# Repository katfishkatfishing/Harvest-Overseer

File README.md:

# Harvest-Overseer 
>Built for third space Hack Club! - Week 1️  
_It all started when two unemployed dudes stumbled upon a third, equally unemployed dude. Unburdened by 9-to-5s (erm but we have 9-5s for school) and fuelled by sheer ambition, the trio tries their best to tackle thirdspace._

## Project Overview 
**Harvest-Overseer** is a stationary, comprehensive agricultural monitor that measures soil pH, moisture levels, nutrient concentrations (NPK), and light intensity. It displays the data of the plant and soil's health on an LCD screen to let you easily know what your plant needs. It displays real-time health diagnostics on an integrated LCD screen so you always know exactly what your plants need to thrive.

### Key Features
**Monitors the soil:** Monitors pH balance and NPK (_Nitrogen, Phosphorus, Potassium_) concentrations.\
**Monitors soil humidity:** Measures the humidity of the soil and computes whether you need to water your plant or not.\
**Monitors light intensity:** Tracks daily ambient light exposures to ensure optimal photosynthesis conditions.\
**Display:** Instant visual updates and shows you clearly what your plant needs.\
**Battery Powered:** Sensor node is battery powered.  

## PCB & Hardware Architecture 
### Master Node (the screen part)
The Master Node receives sensor data, handles system logic, and drives the local LCD status display.
+ <ins>MCU</ins> `ESP32-S3-WROOM-1-N16R8` connects to sensor node to receive data and drive display.
+ <ins>Display</ins> `7-Pin SPI lcd` 3.5 Inch 480*320 SPI TFT LCD Module.
+ <ins>Power</ins> `TP4056 charging power module board` for USB-C power and battery charging, and a `TPS7133Q` (LDO) that converts 4.2V to 3.3V.

_Master Unit PCB and Schematics_
<table>
  <tr>
    <td align="center">
      <br>
      Schematic
    </td>
    <td align="center">
      <br>
      PCB Trace Routing
    </td>
  </tr>
  <tr>
    <td align="center">
       <br>
      3D PCB Render (Top view)
    </td>
    <td align="center">
      <br>
      3D PCB Render (Bottom view)
    </td>
  </tr>
</table>

### Sensor Node
The Sensor Node is an autonomous, low-power unit placed in the soil bed to read the pH, moisture, light, and NPK levels, transmitting readings via ESP-NOW back to the Master Node.

#### Components
+ <ins>MCU</ins> `ESP32-C3-WROOM-02` (compact RISC-V Wi-Fi/BLE MCU) for reading sensors and beaming data to the Master Node.
+ <ins>Power Management</ins> `MCP73871-2CC`, a LiPo/Li-ion charge manager with automatic power path management, allowing simultaneous solar/USB power supply and battery charging.
+ <ins>Timer</ins> `TPL5110`, a system timer that completely cuts off power to the entire node until a scheduled wake interval, reducing standby drain to extend battery life.
+ <ins>Another High-Efficiency Power Management Component</ins>, the `DMG3415U` (P-Channel MOSFET) used to physically power down high-draw soil sensors when the node is sleeping.
+ <ins>Voltage Regulation (LDO)</ins> `HT7333` (Low quiescent current 3.3V regulator for logic and sensor rails).

#### Connectors & Peripherals 
+ <ins>USB-C Interface</ins> a `USB4085` GCT 16-pin USB-C receptacle for charging and power delivery.
+ <ins>Sensor Terminal Blocks</ins> `WAGO 233 Series` tool-less spring-cage terminals for wiring of soil sensors.

<table>
  <tr>
    <td align="center">
      <br>
      Schematic
    </td>
  </tr>
</table>
<table>
  <tr>
    <td align="center">
       <br>
      PCB Trace Routing
    </td>
    <td align="center">
      <br>
      3D PCB Render
    </td>
  </tr>
</table>
<table>
  <tr>
    <td align="center">
       <br>
      3D Model
    </td>
    <td align="center">
      <br>
      3D Model
    </td>
  </tr>
</table>

## Display & User Interface
`DLS24035B` for the display (3.5 Inch 480*320 SPI TFT LCD Module with ILI9488 Driver) with a custom case model.
<table>
  <tr>
    <td align="center">
      <br>
      Front View
    </td>
    <td align="center">
      <br>
      Bottom View
    </td>
  </tr>
</table>

_Here's a photo of the Master Node PCB in the case._
<table>
  <tr>
    <td align="center">
      <br>
      Master Node 3D PCB in case
    </td>
    <td align="center">
      <br>
      Master Node 3D PCB model
    </td>
  </tr>
</table>

_Some display ui (done in the Figma software)_
<table>
  <tr>
    <td align="center">
      <br>
      Plant in good helth
    </td>
    <td align="center">
      <br>
      Plant is unhelth
    </td>
  </tr>
</table>

## Components Used
+ ESP32-S3-WROOM-1-N16N
+ 14-pin socket (Conn_01x14_Socket)
+ TP4056 charging power module board
+ TPS7133Q LDO
+ ESP32-C3-WROOM-02
+ MCP73871-2CC
+ TPL5110
+ DMG3415U
+ HT7333_C2684634
+ USB-C receptacle GCT_USB4085
+ Terminal block WAGO_233-508_2x08
+ Terminal block WAGO_233-508_2x04
+ Button switch SW_SPST_B3U-1000P
+ LED_SMD_0603
+ 10µF capacitor SMD 0402
+ 68k, 10k, 2k, 100k, 5.1k resistor SMD 0603
+ 470R resistor SMD 0402
+ DLS24035B (3.5inch 480*320 SPI TFT LCD Module with ILI9488 Driver)

## BOM
| MCU                               | ESP32-C3-WROOM-02                                   | 1   | 1.80  | 1.80  | https://www.aliexpress.com/item/1005003181553659.html                |
| --------------------------------- | --------------------------------------------------- | --- | ----- | ----- | -------------------------------------------------------------------- |
| 2.54mm Female Header              | Conn_01x08_Socket                                   | 2   | 0.15  | 0.75  | https://www.aliexpress.com/w/wholesale-2.54mm-female-header.html     |
| 2.54mm Female Header              | Conn_01x04_Socket                                   | 1   | 0.10  | 0.50  | https://www.aliexpress.com/w/wholesale-2.54mm-female-header.html     |
| 2.54mm Female Header              | Conn_01x02_Socket                                   | 1   | 0.08  | 0.40  | https://www.aliexpress.com/w/wholesale-2.54mm-female-header.html     |
| LiPo/Li-ion Battery Management IC | MCP73871-2CC                                        | 1   | 2.20  | 2.20  | https://www.aliexpress.com/item/1005009931582723.html                |
| Ultra-Low-Power Timer             | TPL5110                                             | 1   | 3.50  | 3.50  | https://www.aliexpress.com/item/1005009324980307.html                |
| P-Channel MOSFET                  | DMG3415U                                            | 1   | 0.09  | 8.50  | https://www.aliexpress.com/item/1005009968198030.html                |
| Low-Power LDO                     | HT7333_C2684634                                     | 1   | 0.10  | 1.00  | https://www.aliexpress.com/item/32697055615.html                     |
| USB-C Receptacle                  | GCT_USB4085                                         | 1   | 0.35  | 1.75  | https://www.aliexpress.com/w/wholesale-16p-usb-c-receptacle.html     |
| Terminal block                    | WAGO_233-508_2x08                                   | 1   | 1.20  | 1.20  | https://www.aliexpress.com/w/wholesale-wago-233.html                 |
| Terminal block                    | WAGO_233-508_2x04                                   | 1   | 0.70  | 0.70  | https://www.aliexpress.com/w/wholesale-wago-233.html                 |
| Button switch                     | SW_SPST_B3U-1000P                                   | 2   | 0.10  | 1.00  | https://www.aliexpress.com/w/wholesale-smd-tactile-switch.html       |
| LED                               | SMD_0603                                            | 3   | 0.01  | 0.80  | https://www.aliexpress.com/w/wholesale-0603-smd-led.html             |
| Ceramic Capacitor SMD             | 10µF 0402                                           | 3   | 0.01  | 0.90  | https://www.aliexpress.com/w/wholesale-0402-10uf.html                |
| Ceramic Resistor SMD              | 68k 0603                                            | 1   | 0.01  | 0.50  | https://www.aliexpress.com/w/wholesale-smd-resistor-sample-book.html |
| Ceramic Resistor SMD              | 10k 0603                                            | 4   | 0.01  | 0.50  | https://www.aliexpress.com/w/wholesale-smd-resistor-sample-book.html |
| Ceramic Resistor SMD              | 2k 0603                                             | 1   | 0.01  | 0.50  | https://www.aliexpress.com/w/wholesale-smd-resistor-sample-book.html |
| Ceramic Resistor SMD              | 100k 0603                                           | 1   | 0.01  | 0.50  | https://www.aliexpress.com/w/wholesale-smd-resistor-sample-book.html |
| Ceramic Resistor SMD              | 5.1k 0603                                           | 2   | 0.01  | 0.50  | https://www.aliexpress.com/w/wholesale-smd-resistor-sample-book.html |
| Ceramic Resistor SMD              | 470R 0402                                           | 3   | 0.01  | 0.50  | https://www.aliexpress.com/w/wholesale-smd-resistor-sample-book.html |
| Liquid Crystal Display            | DLS24035B                                           | 1   | 9.20  | 9.20  | https://www.aliexpress.com/item/1005005287088814.html                |
| Capacitor SMD                     | 1uF 0603 (C_0402_1005Metric)                        | 1   | 2.27  | 2.27  | https://www.aliexpress.com/item/1005012364450156.html                |
| 2.54mm Female Header              | Conn_01x14_Socket (PinSocket_1x14_P2.54mm_Vertical) | 1   | 2.89  | 2.89  | https://www.aliexpress.com/item/1005003610333849.html                |
| Resistor SMD                      | 10k 0603 (R_0603_1608Metric)                        | 3   | 0.45  | 1.36  | https://www.aliexpress.com/item/1005005677654015.html                |
| Push Button Switch (THT)          | MJTP1243 (SW_PUSH_1P1T_6x3.5mm_H4.3_APEM_MJTP1243)  | 1   | 0.42  | 0.42  | https://www.digikey.com/en/products/detail/apem-inc/MJTP1243/1798039 |
| Side Tactile Switch (SMD)         | TS-1101-C-W (SW-SMD_TC-1101V-C-B-W)                 | 1   | 0.40  | 0.40  | https://item.szlcsc.com/300030.html                                  |
| Power Module                      | TP4056 module (PWRM-TH_TP4056)                      | 1   | 1.73  | 1.73  | https://www.aliexpress.com/item/1005005982385924.html                |
| MCU Module                        | ESP32-S3-WROOM-1-N16R8 (ESP32-S3-WROOM-1_EXP)       | 1   | 4.78  | 4.78  | https://www.aliexpress.com/item/1005005230800143.html                |
| Voltage Regulator IC              | TPS7133 (SOIC-8_3.9x4.9mm_P1.27mm)                  | 1   | 15.36 | 15.36 | https://www.aliexpress.com/item/1005012324115212.html                |

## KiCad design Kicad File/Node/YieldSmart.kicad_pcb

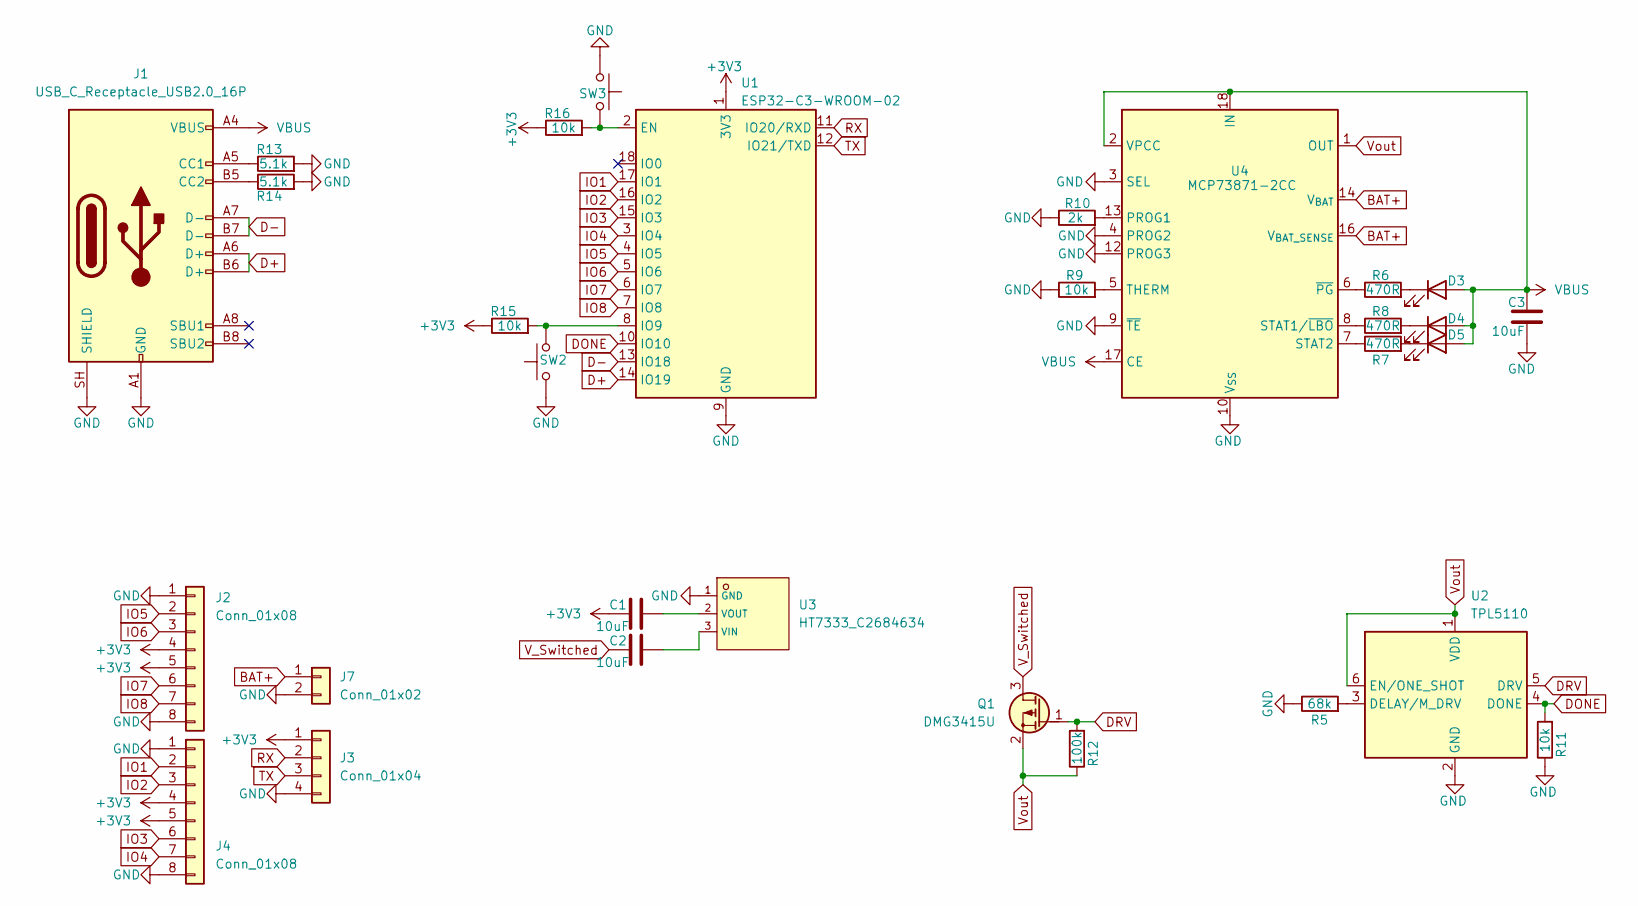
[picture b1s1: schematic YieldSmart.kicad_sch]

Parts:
C1, C2, C3: 10uF; C_0402_1005Metric_Pad0.74x0.62mm_HandSolder
D3, D4, D5: LED; LED_0603_1608Metric_Pad1.05x0.95mm_HandSolder
J1: USB_C_Receptacle_USB2.0_16P; USB_C_Receptacle_GCT_USB4085
J2, J4: Conn_01x08; PinHeader_1x08_P2.54mm_Vertical
J3: Conn_01x04; PinHeader_1x04_P2.54mm_Vertical
J7: Conn_01x02; PinHeader_1x02_P2.54mm_Vertical
Q1: DMG3415U; SOT-23
R5: 68k; R_0603_1608Metric_Pad0.98x0.95mm_HandSolder
R6, R7, R8: 470R; R_0402_1005Metric_Pad0.72x0.64mm_HandSolder
R9, R11, R15, R16: 10k; R_0603_1608Metric_Pad0.98x0.95mm_HandSolder
R10: 2k; R_0603_1608Metric_Pad0.98x0.95mm_HandSolder
R12: 100k; R_0603_1608Metric_Pad0.98x0.95mm_HandSolder
R13, R14: 5.1k; R_0603_1608Metric_Pad0.98x0.95mm_HandSolder
SW2, SW3: SW_Push; SW_SPST_B3U-1000P
U1: ESP32-C3-WROOM-02
U2: TPL5110; SOT-23-6
U3: HT7333_C2684634; C2684634_SOT-23-3_L2_9-W1_6-P1_90-LS2_8-BR; LCSC C2684634
U4: MCP73871-2CC; QFN-20-1EP_4x4mm_P0.5mm_EP2.5x2.5mm

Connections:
+3V3: C1.1, J2.4, J2.5, J3.1, J4.4, J4.5, R15.1, R16.1, U1.1 (3V3)
BAT+: J7.1, U4.14 (V_{BAT}), U4.15 (V_{BAT}), U4.16 (V_{BAT_SENSE})
D+: J1.A6 (D+), J1.B6 (D+), U1.14 (IO19)
D-: J1.A7 (D-), J1.B7 (D-), U1.13 (IO18)
DONE: R11.2, U1.10 (IO10), U2.4 (DONE)
DRV: Q1.1 (G), R12.2, U2.5 (DRV)
GND: C3.2, J1.A1 (GND), J1.A12 (GND), J1.B1 (GND), J1.B12 (GND), J1.SH (SHIELD), J2.1, J2.8, J3.4, J4.1, J4.8, J7.2, R5.1, R9.1, R10.1, R11.1, R13.2, R14.2, SW2.2, SW3.2, U1.9 (GND), U1.19 (GND), U2.2 (GND), U3.1 (GND), U4.3 (SEL), U4.4 (PROG2), U4.9 (~TE), U4.10 (V_{SS}), U4.11 (V_{SS}), U4.12 (PROG3), U4.21 (V_{SS})
IO1: J4.2, U1.17 (IO1)
IO2: J4.3, U1.16 (IO2)
IO3: J4.6, U1.15 (IO3)
IO4: J4.7, U1.3 (IO4)
IO5: J2.2, U1.4 (IO5)
IO6: J2.3, U1.5 (IO6)
IO7: J2.6, U1.6 (IO7)
IO8: J2.7, U1.7 (IO8)
unnamed: D3.1 (K), R6.2
unnamed: D4.1 (K), R8.2
unnamed: D5.1 (K), R7.2
unnamed: J1.A5 (CC1), R13.1
unnamed: J1.B5 (CC2), R14.1
unnamed: R16.2, SW3.1, U1.2 (EN)
unnamed: R15.2, SW2.1, U1.8 (IO9)
unnamed: R5.2, U2.3 (DELAY/M_DRV)
unnamed: C2.2, U3.3 (VIN)
unnamed: C1.2, U3.2 (VOUT)
unnamed: R10.2, U4.13 (PROG1)
unnamed: R8.1, U4.8 (STAT1/~LBO)
unnamed: R7.1, U4.7 (STAT2)
unnamed: R9.2, U4.5 (THERM)
unnamed: R6.1, U4.6 (~PG)
RX: J3.2, U1.11 (IO20/RXD)
TX: J3.3, U1.12 (IO21/TXD)
VBUS: C3.1, D3.2 (A), D4.2 (A), D5.2 (A), J1.A4 (VBUS), J1.A9 (VBUS), J1.B4 (VBUS), J1.B9 (VBUS), U4.2 (VPCC), U4.17 (CE), U4.18 (IN), U4.19 (IN)
V_Switched: C2.1, Q1.3 (D)
Vout: Q1.2 (S), R12.1, U2.1 (VDD), U2.6 (EN/ONE_SHOT), U4.1 (OUT), U4.20 (OUT)

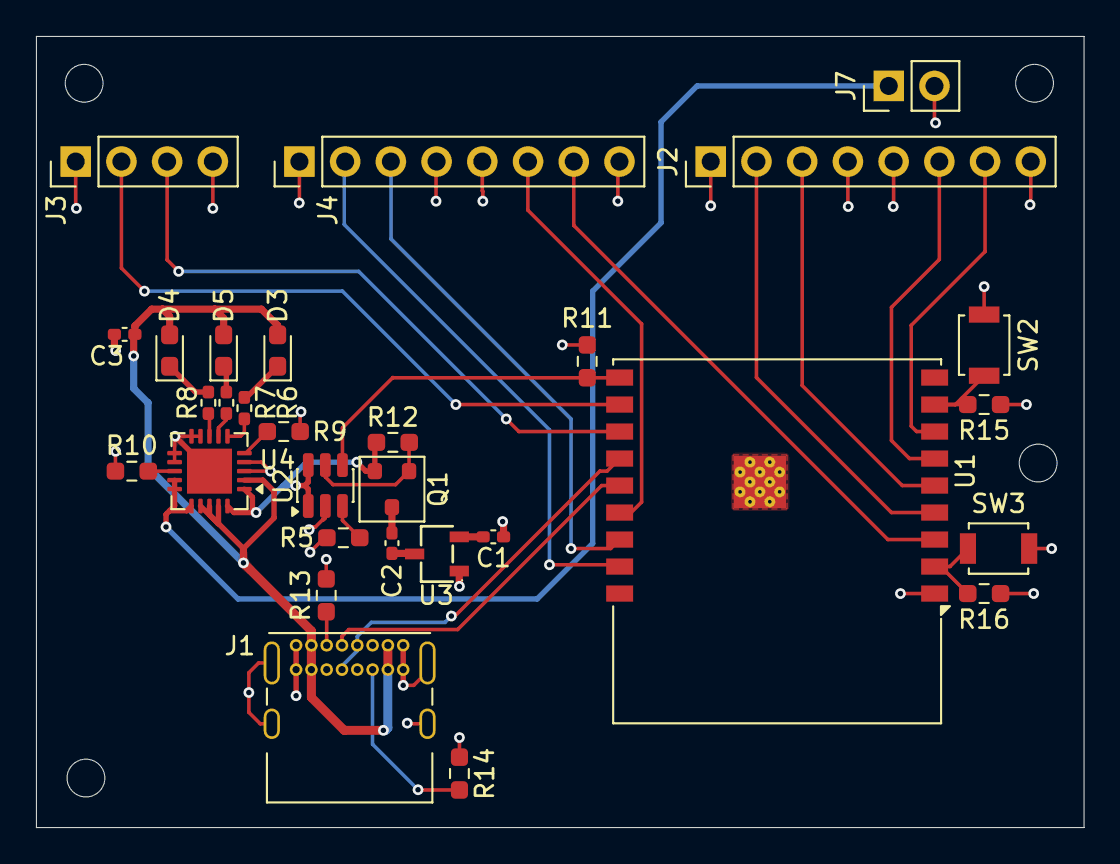
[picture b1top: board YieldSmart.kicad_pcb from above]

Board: 4 copper layers, 58.2 x 43.9 mm, 30 parts (0 on the bottom side), 35 nets.

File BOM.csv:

Item,Parts,Qty.,Unit price(USD),Price per lot(USD),Source
MCU, ESP32-C3-WROOM-02, 1, 1.80, 1.80, https://www.aliexpress.com/item/1005003181553659.html
2.54mm Female Header, Conn_01x08_Socket, 2, 0.15, 0.75, https://www.aliexpress.com/w/wholesale-2.54mm-female-header.html
2.54mm Female Header, Conn_01x04_Socket, 1, 0.10, 0.50, https://www.aliexpress.com/w/wholesale-2.54mm-female-header.html
2.54mm Female Header, Conn_01x02_Socket, 1, 0.08, 0.40, https://www.aliexpress.com/w/wholesale-2.54mm-female-header.html
LiPo/Li-ion Battery Management IC, MCP73871-2CC, 1, 2.20, 2.20, https://www.aliexpress.com/item/1005009931582723.html
Ultra-Low-Power Timer, TPL5110, 1, 3.50, 3.50, https://www.aliexpress.com/item/1005009324980307.html
P-Channel MOSFET, DMG3415U, 1, 0.09, 8.50, https://www.aliexpress.com/item/1005009968198030.html
Low-Power LDO, HT7333_C2684634, 1, 0.10, 1.00, https://www.aliexpress.com/item/32697055615.html
USB-C Receptacle, GCT_USB4085, 1, 0.35, 1.75, https://www.aliexpress.com/w/wholesale-16p-usb-c-receptacle.html
Terminal block, WAGO_233-508_2x08, 1, 1.20, 1.20, https://www.aliexpress.com/w/wholesale-wago-233.html
Terminal block, WAGO_233-508_2x04, 1, 0.70, 0.70, https://www.aliexpress.com/w/wholesale-wago-233.html
Button switch, SW_SPST_B3U-1000P, 2, 0.10, 1.00, https://www.aliexpress.com/w/wholesale-smd-tactile-switch.html
LED, SMD_0603, 3, 0.01, 0.80, https://www.aliexpress.com/w/wholesale-0603-smd-led.html
Ceramic Capacitor SMD, 10µF 0402, 3, 0.01, 0.90, https://www.aliexpress.com/w/wholesale-0402-10uf.html
Ceramic Resistor SMD, 68k 0603, 1, 0.01, 0.50, https://www.aliexpress.com/w/wholesale-smd-resistor-sample-b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
Ceramic Resistor SMD, 10k 0603, 4, 0.01, 0.50, https://www.aliexpress.com/w/wholesale-smd-resistor-sample-b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
Ceramic Resistor SMD, 2k 0603, 1, 0.01, 0.50, https://www.aliexpress.com/w/wholesale-smd-resistor-sample-b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
Ceramic Resistor SMD, 100k 0603, 1, 0.01, 0.50, https://www.aliexpress.com/w/wholesale-smd-resistor-sample-b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
Ceramic Resistor SMD, 5.1k 0603, 2, 0.01, 0.50, https://www.aliexpress.com/w/wholesale-smd-resistor-sample-b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
Ceramic Resistor SMD, 470R 0402, 3, 0.01, 0.50, https://www.aliexpress.com/w/wholesale-smd-resistor-sample-b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
Liquid Crystal Display, DLS24035B, 1, 9.20, 9.20, https://www.aliexpress.com/item/1005005287088814.html
<!-- BOM generated in https://md-to.com/csv-to-markdown-table/ -->

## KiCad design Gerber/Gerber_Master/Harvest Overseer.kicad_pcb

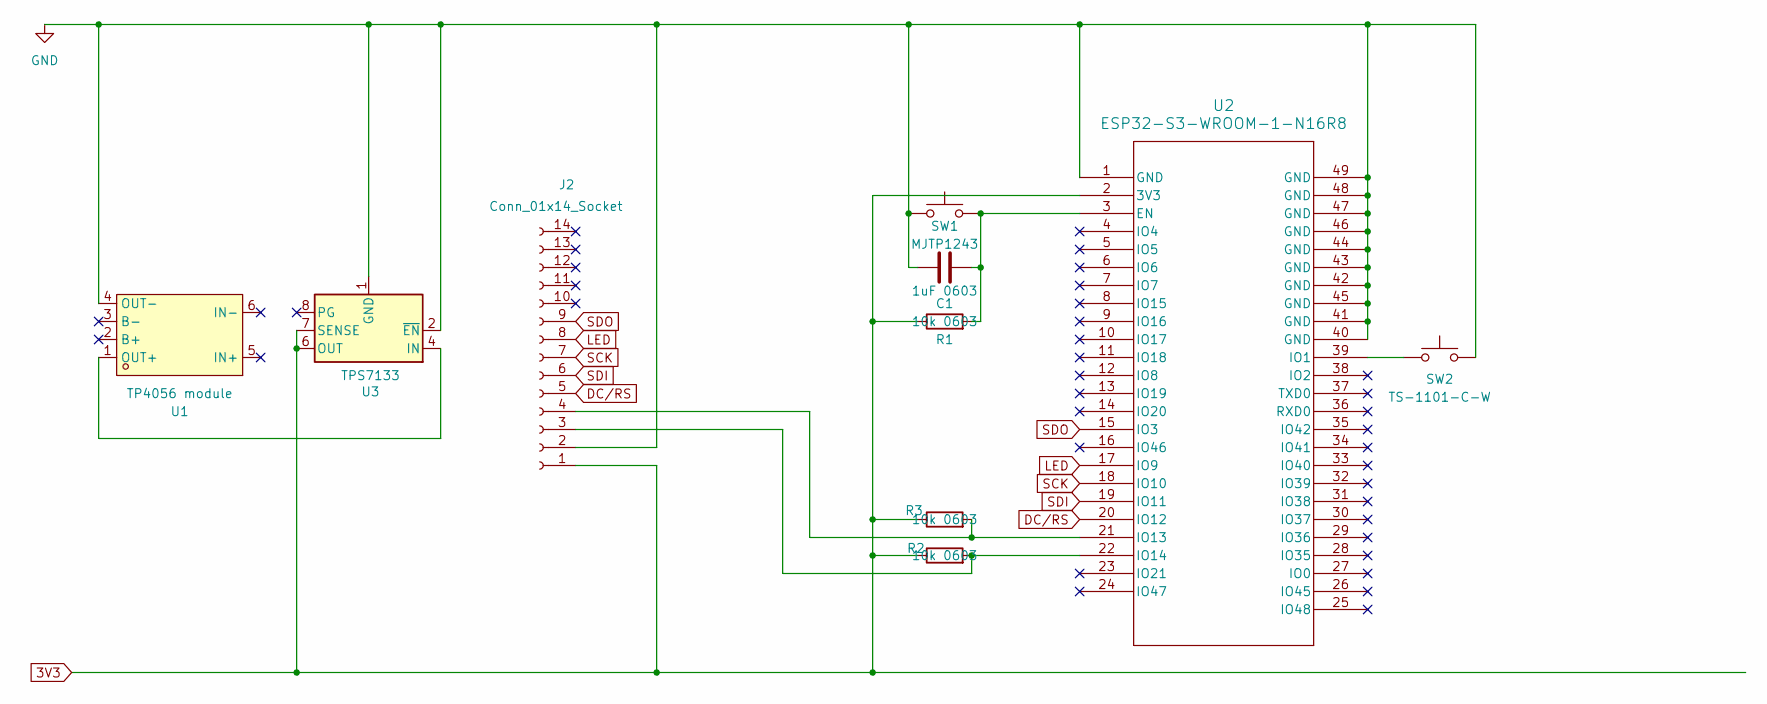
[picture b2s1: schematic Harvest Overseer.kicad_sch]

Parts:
C1: 1uF 0603; C_0402_1005Metric
J2: Conn_01x14_Socket; PinSocket_1x14_P2.54mm_Vertical
R1, R2, R3: 10k 0603; R_0603_1608Metric
SW1: MJTP1243; SW_PUSH_1P1T_6x3.5mm_H4.3_APEM_MJTP1243
SW2: TS-1101-C-W; SW-SMD_TC-1101V-C-B-W
U1: TP4056 module; PWRM-TH_TP4056; MPN TP4056充电源模块板(Type-C); LCSC Part C9900049108
U2: ESP32-S3-WROOM-1-N16R8; ESP32-S3-WROOM-1_EXP
U3: TPS7133; SOIC-8_3.9x4.9mm_P1.27mm

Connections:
3V3: J2.1, R1.1, R2.1, R3.1, U2.2 (3V3), U3.5 (OUT), U3.6 (OUT), U3.7 (SENSE)
DC/RS: J2.5, U2.20 (IO12)
GND: C1.1, J2.2, SW1.1, SW2.2, U1.4 (OUT-), U2.1 (GND), U2.40 (GND), U2.41 (GND), U2.42 (GND), U2.43 (GND), U2.44 (GND), U2.45 (GND), U2.46 (GND), U2.47 (GND), U2.48 (GND), U2.49 (GND), U3.1 (GND), U3.2 (~EN)
LED: J2.8, U2.17 (IO9)
unnamed: J2.3, R2.2, U2.22 (IO14)
unnamed: J2.4, R3.2, U2.21 (IO13)
unnamed: U1.1 (OUT+), U3.3 (IN), U3.4 (IN)
unnamed: C1.2, R1.2, SW1.2, U2.3 (EN)
unnamed: SW2.1, U2.39 (IO1)
SCK: J2.7, U2.18 (IO10)
SDI: J2.6, U2.19 (IO11)
SDO: J2.9, U2.15 (IO3)

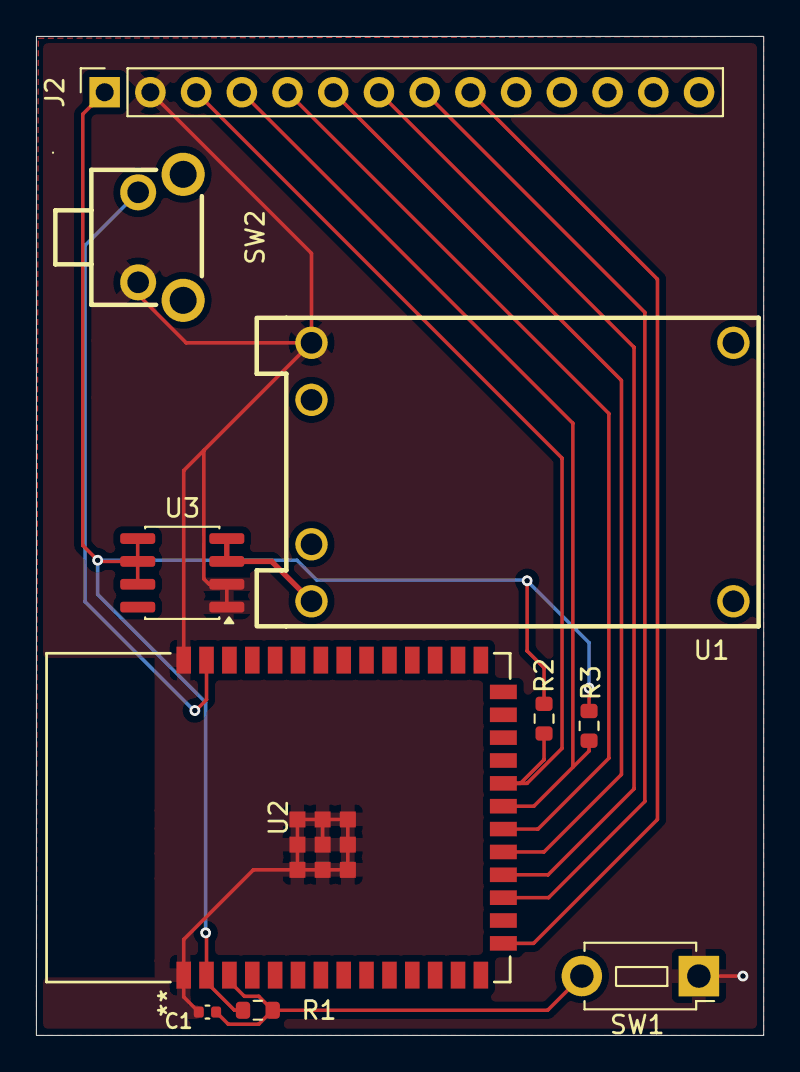
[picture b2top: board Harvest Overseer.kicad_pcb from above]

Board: 2 copper layers, 40.4 x 55.5 mm, 10 parts (0 on the bottom side), 12 nets.

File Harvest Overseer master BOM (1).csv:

"Qty","Value","Footprint","Price per lot (usd)","Source"
"1","1uF 0603","Capacitor_SMD:C_0402_1005Metric","2.27","https://www.aliexpress.com/item/1005012364450156.html?spm=a2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"
"1","Conn_01x14_Socket","Connector_PinSocket_2.54mm:PinSocket_1x14_P2.54mm_Vertical","2.89","https://www.aliexpress.com/item/1005003610333849.html?spm=a2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"
"3","10k 0603","Resistor_SMD:R_0603_1608Metric","1.36","https://www.aliexpress.com/item/1005005677654015.html?spm=a2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"
"1","MJTP1243","Button_Switch_THT:SW_PUSH_1P1T_6x3.5mm_H4.3_APEM_MJTP1243","0.42","https://www.digikey.com/en/products/detail/apem-inc/MJTP1243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"
"1","TS-1101-C-W","sidebutton:SW-SMD_TC-1101V-C-B-W","0.40","https://item.szlcsc.com/300030.html"
"1","TP4056 module","easyeda2kicad:PWRM-TH_TP4056","1.73","https://www.aliexpress.com/item/1005005982385924.html?spm=a2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"
"1","ESP32-S3-WROOM-1-N16R8","esp32 somethingsomethingsomething:ESP32-S3-WROOM-1_EXP","4.78","https://www.aliexpress.com/item/1005005230800143.html?spm=a2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"
"1","TPS7133","Package_SO:SOIC-8_3.9x4.9mm_P1.27mm","15.36","https://www.aliexpress.com/item/1005012324115212.html?spm=a2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"
